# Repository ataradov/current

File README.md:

# Current Profiler
This is a current profiler for low power devices (up to 100 mA).
Sorry, no detailed description at this time.

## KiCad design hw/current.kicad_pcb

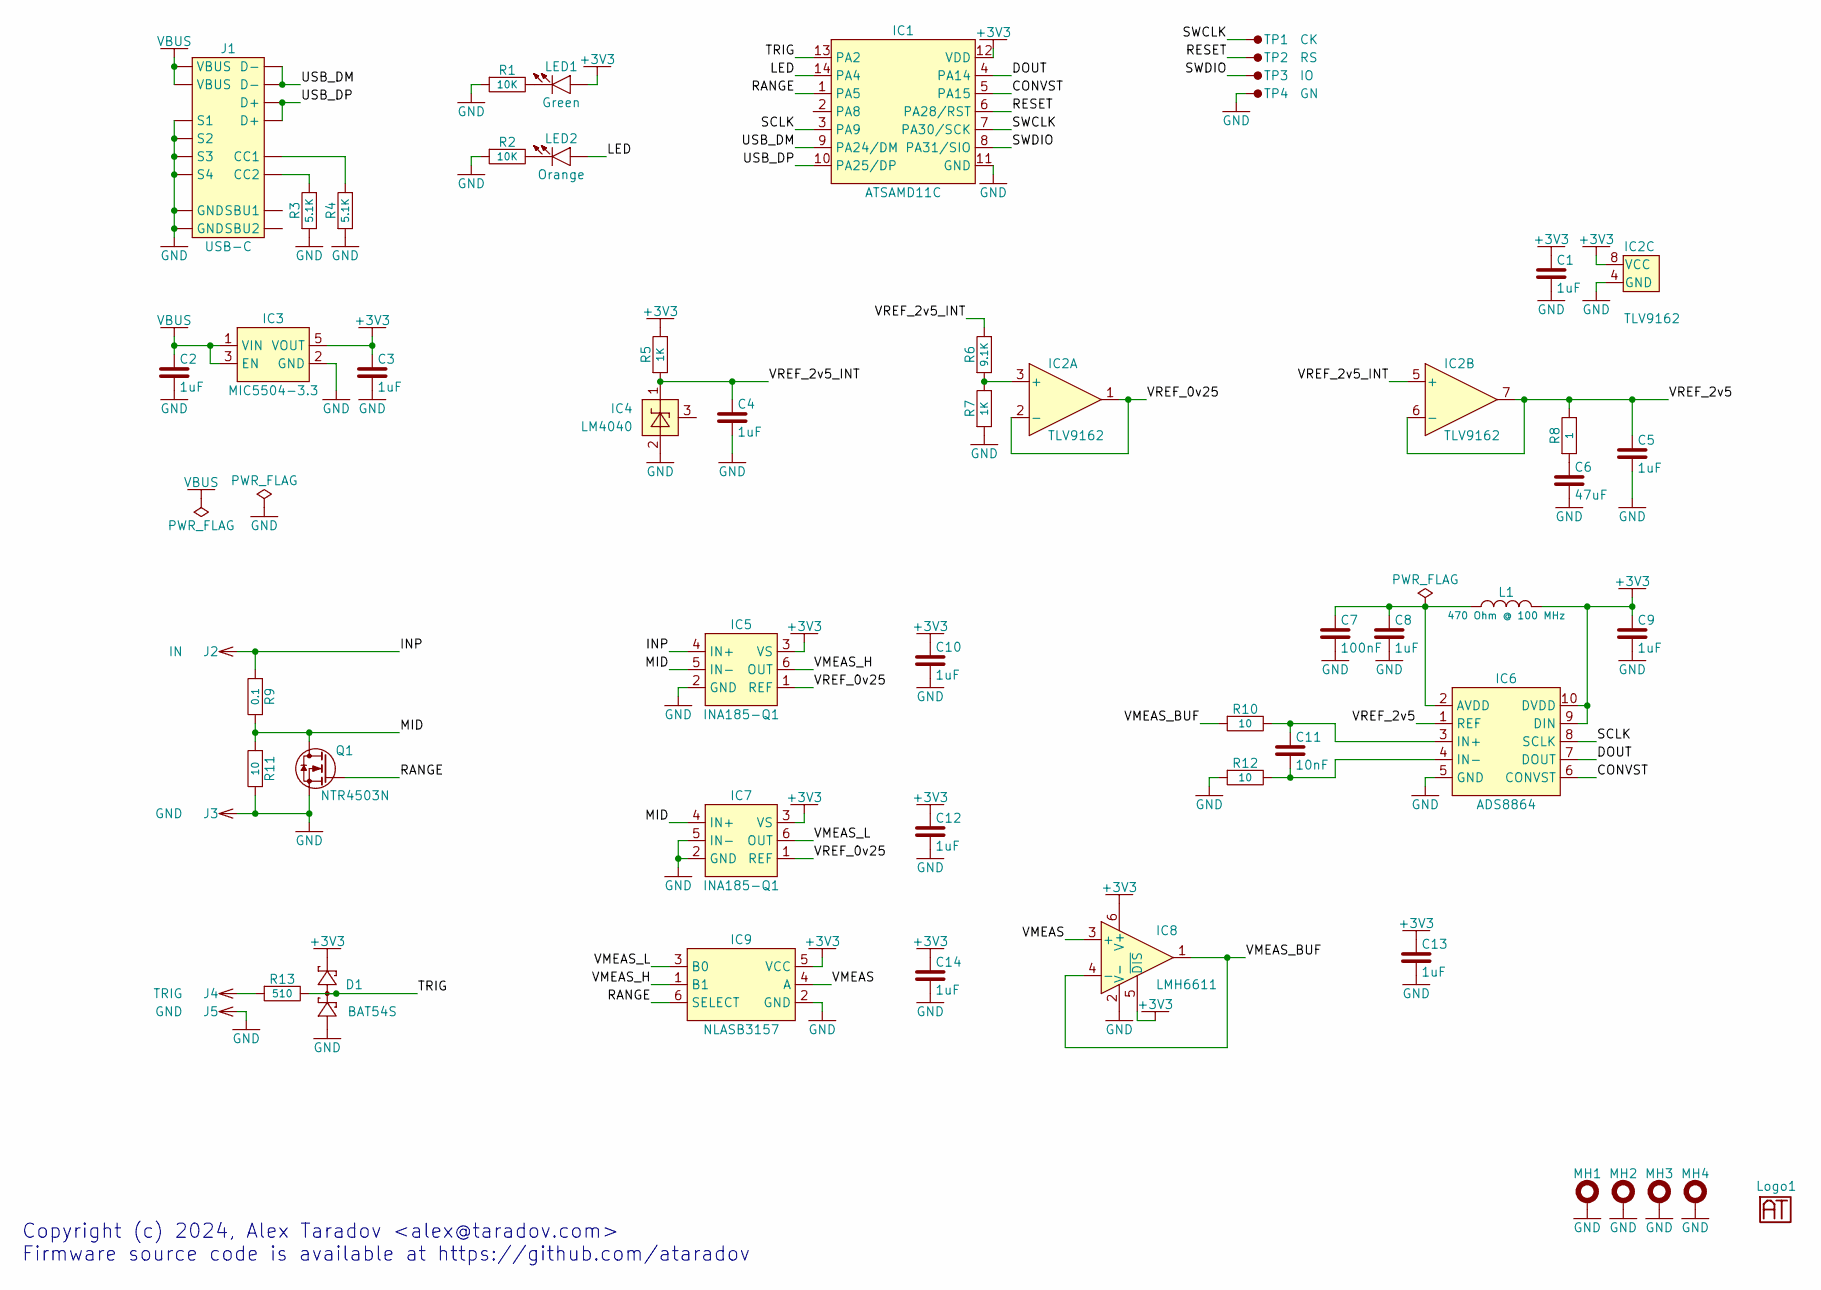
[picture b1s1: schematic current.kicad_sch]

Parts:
C1, C2, C3, C4, C5, C8, C9, C10, C12, C13, C14: 1uF; 0603
C6: 47uF; 0603
C7: 100nF; 0603
C11: 10nF; 0603
D1: BAT54S; SOT-23
IC1: ATSAMD11C; SOIC-14
IC2: TLV9162; SO-8
IC3: MIC5504-3.3; SOT-23-5
IC4: LM4040; SOT-23
IC5, IC7: INA185-Q1; SOT-363(SC-70-6)
IC6: ADS8864; MSOP-10-0.5mm
IC8: LMH6611; SOT-23-6
IC9: NLASB3157; SOT-363(SC-70-6)
J1: USB-C
J2: IN; Pin-2.54mm
J3, J5: GND; Pin-2.54mm
J4: TRIG; Pin-2.54mm
L1: 470 Ohm @ 100 MHz; 0603
LED1: Green; 0603_LED
LED2: Orange; 0603_LED
Logo1: Logo; Logo-Small
MH1, MH2, MH3, MH4: MH-2.5mm-4.0mm
Q1: NTR4503N; SOT-23
R1, R2: 10K; 0603
R3, R4: 5.1K; 0603
R5, R7: 1K; 0603
R6: 9.1K; 0603
R8: 1; 0603
R9: 0.1; 0805
R10, R12: 10; 0603
R11: 10; 0805
R13: 510; 0603
TP1: CK; TestPoint-1.27mm
TP2: RS; TestPoint-1.27mm
TP3: IO; TestPoint-1.27mm
TP4: GN; TestPoint-1.27mm

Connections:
+3V3: C1.2, C3.2, C9.2, C10.2, C12.2, C13.2, C14.2, D1.2, IC1.12 (VDD), IC2.8 (VCC), IC3.5 (VOUT), IC5.3 (VS), IC6.9 (DIN), IC6.10 (DVDD), IC7.3 (VS), IC8.5 (~DIS), IC8.6 (V+), IC9.5 (VCC), L1.2, LED1.1 (A), R5.2
/CONVST: IC1.5 (PA15), IC6.6 (CONVST)
/DOUT: IC1.4 (PA14), IC6.7 (DOUT)
/INP: IC5.4 (IN+), J2.1, R9.1
/LED: IC1.14 (PA4), LED2.1 (A)
/MID: IC5.5 (IN-), IC7.4 (IN+), Q1.3 (D), R9.2, R11.1
/RANGE: IC1.1 (PA5), IC9.6 (SELECT), Q1.1 (G)
/RESET: IC1.6 (PA28/RST), TP2.1
/SCLK: IC1.3 (PA9), IC6.8 (SCLK)
/SWCLK: IC1.7 (PA30/SCK), TP1.1
/SWDIO: IC1.8 (PA31/SIO), TP3.1
/TRIG: D1.3, IC1.13 (PA2), R13.2
/USB_DM: IC1.9 (PA24/DM), J1.D-1 (D-), J1.D-2 (D-)
/USB_DP: IC1.10 (PA25/DP), J1.D+1 (D+), J1.D+2 (D+)
/VMEAS: IC8.3 (+), IC9.4 (A)
/VMEAS_BUF: IC8.1, IC8.4 (-), R10.1
/VMEAS_H: IC5.6 (OUT), IC9.1 (B1)
/VMEAS_L: IC7.6 (OUT), IC9.3 (B0)
/VREF_0v25: IC2.1, IC2.2 (-), IC5.1 (REF), IC7.1 (REF)
/VREF_2v5: C5.2, IC2.6 (-), IC2.7, IC6.1 (REF), R8.2
/VREF_2v5_INT: C4.2, IC2.5 (+), IC4.1 (K), R5.1, R6.2
GND: C1.1, C2.1, C3.1, C4.1, C5.1, C6.1, C7.1, C8.1, C9.1, C10.1, C12.1, C13.1, C14.1, D1.1, IC1.11 (GND), IC2.4 (GND), IC3.2 (GND), IC4.2 (A), IC5.2 (GND), IC6.5 (GND), IC7.2 (GND), IC7.5 (IN-), IC8.2 (V-), IC9.2 (GND), J1.GND1 (GND), J1.GND2 (GND), J1.S1, J1.S2, J1.S3, J1.S4, J3.1, J5.1, MH1.1, MH2.1, MH3.1, MH4.1, Q1.2 (S), R1.1, R2.1, R3.1, R4.1, R7.1, R11.2, R12.1, TP4.1
unnamed: C6.2, R8.1
unnamed: IC2.3 (+), R6.1, R7.2
unnamed: C7.2, C8.2, IC6.2 (AVDD), L1.1
unnamed: C11.2, IC6.3 (IN+), R10.2
unnamed: C11.1, IC6.4 (IN-), R12.2
unnamed: J1.CC1, R4.2
unnamed: J1.CC2, R3.2
unnamed: J4.1, R13.1
unnamed: LED1.2 (K), R1.2
unnamed: LED2.2 (K), R2.2
VBUS: C2.2, IC3.1 (VIN), IC3.3 (EN), J1.VBUS1 (VBUS), J1.VBUS2 (VBUS)

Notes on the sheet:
Copyright (c) 2024, Alex Taradov <alex@taradov.com> Firmware source code is available at https://github.com/ataradov

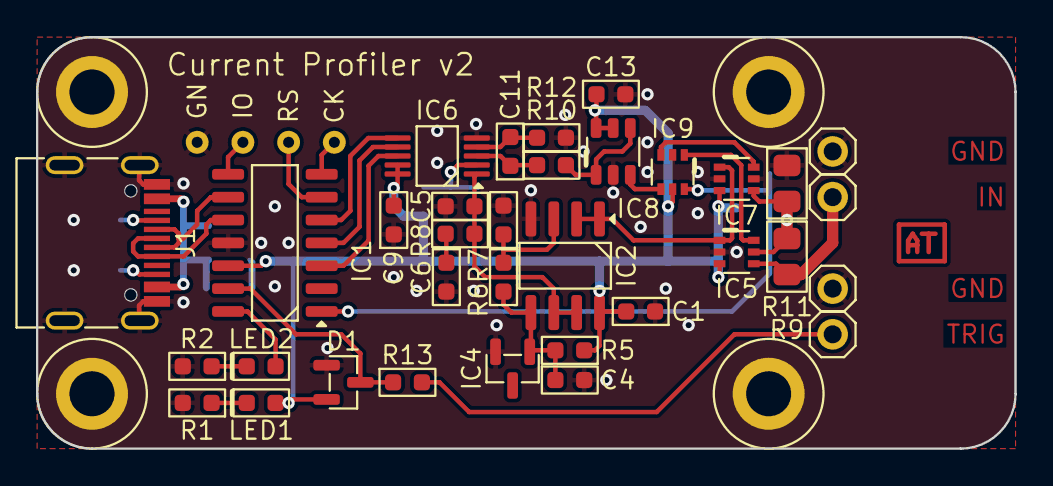
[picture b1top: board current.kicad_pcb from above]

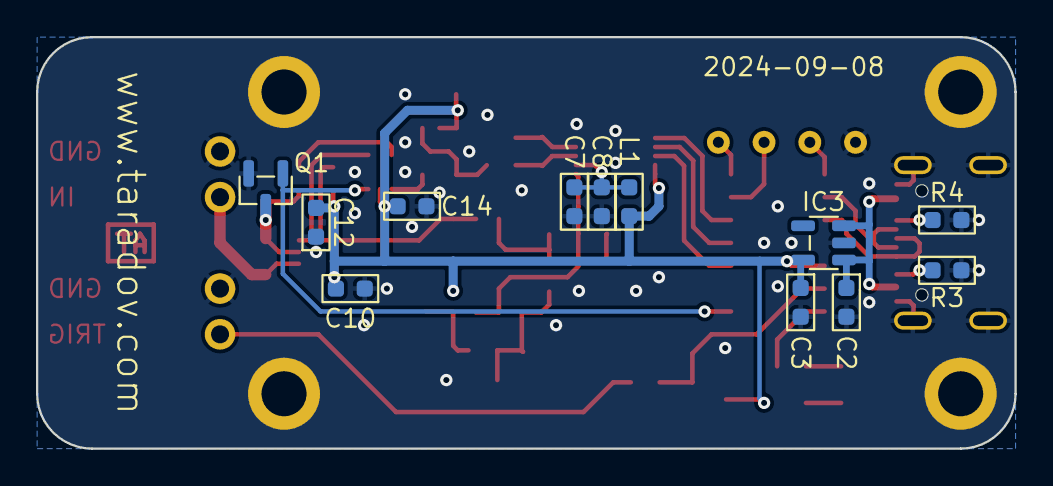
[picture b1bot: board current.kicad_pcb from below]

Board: 2 copper layers, 54.4 x 22.9 mm, 55 parts (12 on the bottom side), 33 nets.

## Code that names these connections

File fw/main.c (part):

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#define GCLK_ID_DPLL_48M       2
#define GCLK_ID_DPLL_96M       3

HAL_GPIO_PIN(TRIG,             A, 2);
HAL_GPIO_PIN(LED,              A, 4);
HAL_GPIO_PIN(RANGE,            A, 5);
HAL_GPIO_PIN(SCLK,             A, 9);
HAL_GPIO_PIN(DOUT,             A, 14);
HAL_GPIO_PIN(CONVST,           A, 15);

#define CTRL_ENABLE            (1 << 0)
#define CTRL_RANGE             (1 << 1)
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static void set_range(bool range)
{
  g_range = range << 8;
  HAL_GPIO_RANGE_write(range);
}

//-----------------------------------------------------------------------------
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
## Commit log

2025-11-03 Initial release
2025-11-04 Added GUI screenshot

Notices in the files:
fw/main.c:
SPDX-License-Identifier: BSD-3-Clause
Copyright (c) 2024, Alex Taradov <alex@taradov.com>. All rights reserved.
